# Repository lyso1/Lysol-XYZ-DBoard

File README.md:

# Lysol-XYZ-DBoard
An edited version of the daughter board that was used on XYZ's B-KEN_KO.
This version of the xyz dboard uses the same pinout as c3 unified dboard used on many other boards and other vendors sell. 

This version exists because the original lacked a resetable fuse for over current as well as a diode for some over volt protection. 

There's a pre made panel gerber/project file as well as a BOM and CPL file for JLCPCB prodution and assembly that'll make around 225 dboards from one order at the minimum of 5 panels/pcbs. if you need to change anything bom wise, i'd suggest doing so through the JLCPCB KIcad v6 plugin for easy modifications.

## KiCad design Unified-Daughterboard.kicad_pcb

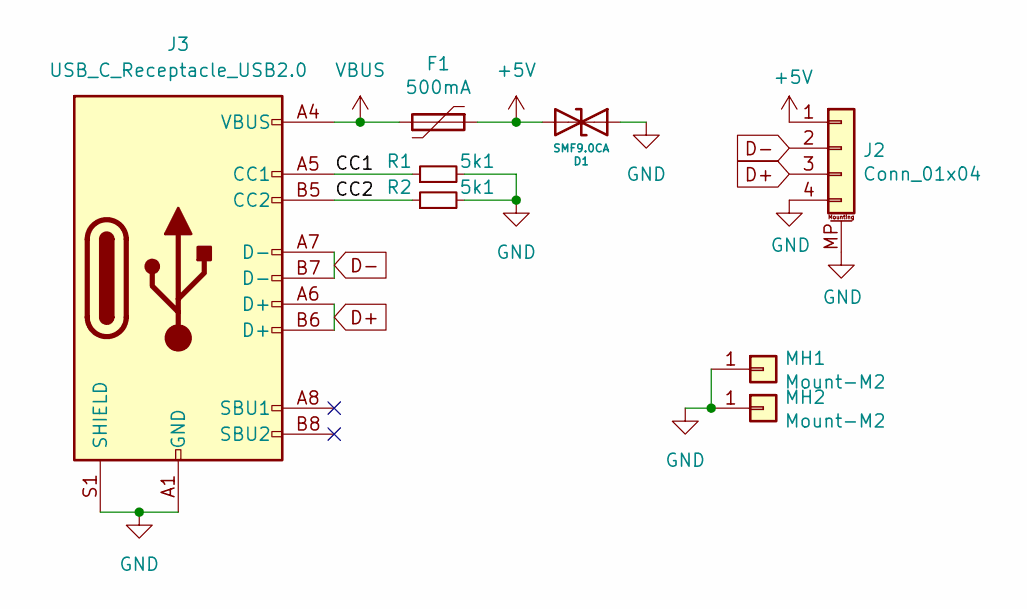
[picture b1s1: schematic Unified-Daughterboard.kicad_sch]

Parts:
D1: SMF9.0CA; D_SOD-123; Manufacturer Part No SMF9.0CA; LCSC Part No C123799
F1: 500mA; Fuse_1206_3216Metric
J2: Conn_01x04; JST-SR-4
J3: USB_C_Receptacle_USB2.0; USB_C_Receptacle_HRO_TYPE-C-31-M-12
MH1, MH2: Mount-M2; MountingHole_3.2mm_M3_Pad_Via
R1, R2: 5k1; R_0402_1005Metric

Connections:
+5V: D1.2 (A2), F1.1, J2.1
/CC1: J3.A5 (CC1), R1.1
/CC2: J3.B5 (CC2), R2.1
D+: J2.3, J3.A6 (D+), J3.B6 (D+)
D-: J2.2, J3.A7 (D-), J3.B7 (D-)
GND: D1.1 (A1), J2.4, J2.MP (MountPin), J3.A1 (GND), J3.A12 (GND), J3.B1 (GND), J3.B12 (GND), J3.S1 (SHIELD), MH1.1, MH2.1, R1.2, R2.2
VBUS: F1.2, J3.A4 (VBUS), J3.A9 (VBUS), J3.B4 (VBUS), J3.B9 (VBUS)

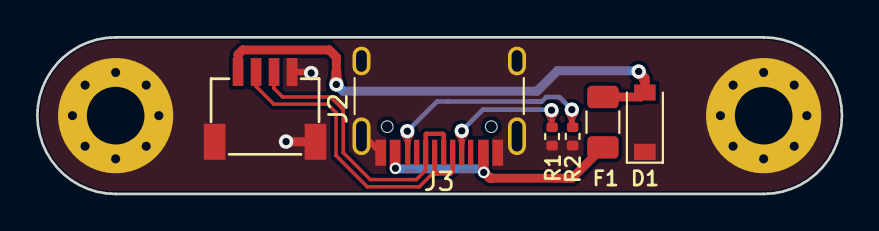
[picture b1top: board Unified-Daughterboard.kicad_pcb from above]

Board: 2 copper layers, 44.7 x 8.7 mm, 8 parts (0 on the bottom side), 7 nets.

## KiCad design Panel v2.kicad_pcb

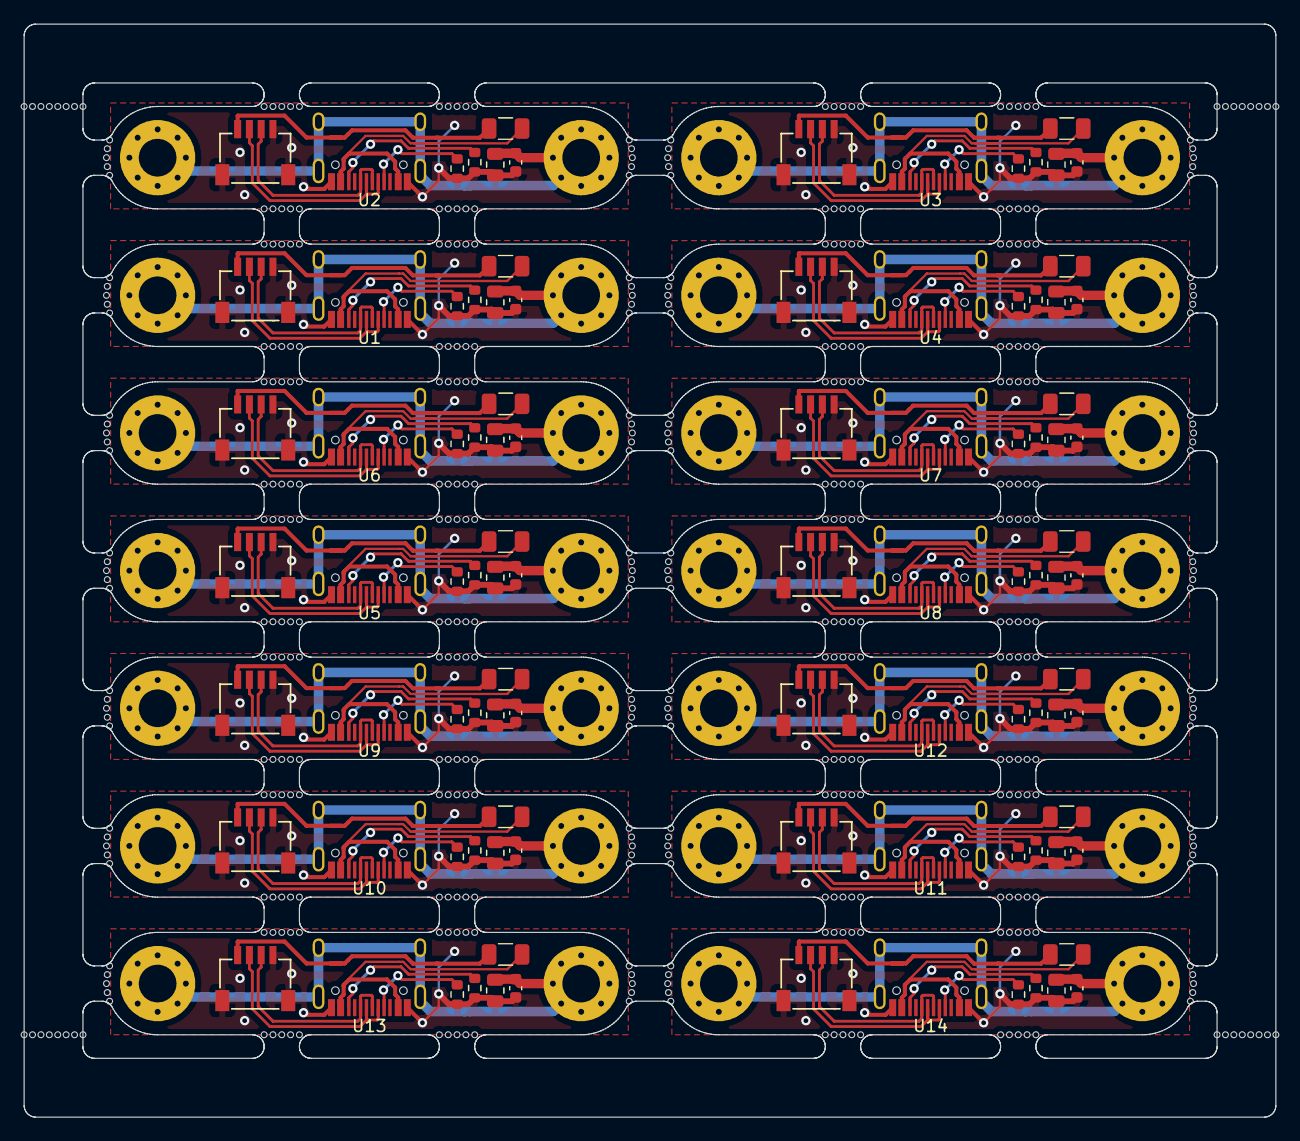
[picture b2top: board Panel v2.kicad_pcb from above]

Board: 2 copper layers, 106.4 x 92.9 mm, 126 parts (0 on the bottom side), 42 nets.

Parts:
C1, C2, C3, C4, C5, C6, C7, C8, C9, C10, C11, C12, C13, C14: 4.7n; C_0603_1608Metric
F1, F2, F3, F4, F5, F6, F7, F8, F9, F10, F11, F12, F13, F14: 500mA; Fuse_1206_3216Metric
J1, J2, J3, J4, J5, J6, J7, J8, J9, J10, J11, J12, J13, J14: Conn_01x04; JST-SR-4
MH1, MH2, MH3, MH4, MH5, MH6, MH7, MH8, MH9, MH10, MH11, MH12, MH13, MH14, MH15, MH16, MH17, MH18, MH19, MH20, MH21, MH22, MH23, MH24, MH25, MH26, MH27, MH28: Mount-M2; MountingHole_3.2mm_M3_Pad_Via
R1, R4, R9, R12, R13, R15, R20, R23, R25, R26, R35, R36, R39, R42: 1M; R_0805_2012Metric
R2, R3, R5, R6, R7, R8, R10, R11, R14, R16, R17, R18, R19, R21, R22, R24, R27, R28, R29, R30, R31, R32, R33, R34, R37, R38, R40, R41: 5.1k; R_0603_1608Metric
U1, U2, U3, U4, U5, U6, U7, U8, U9, U10, U11, U12, U13, U14: HRO-TYPE-C-31-M-12

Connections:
Board_0-+5V: F2.1, J1.1
Board_0-GND: C1.1, J1.4, J1.MP (MountPin), R1.1, R5.2, R6.2
Board_0-SHIELD: C1.2, MH1.1, MH5.1, R1.2
Board_1-+5V: F3.1, J2.1
Board_1-GND: C3.1, J2.4, J2.MP (MountPin), R8.2, R9.1, R11.2
Board_1-SHIELD: C3.2, MH4.1, MH8.1, R9.2
Board_2-+5V: F1.1, J4.1
Board_2-GND: C2.1, J4.4, J4.MP (MountPin), R2.2, R3.2, R4.1
Board_2-SHIELD: C2.2, MH2.1, MH3.1, R4.2
Board_3-+5V: F4.1, J8.1
Board_3-GND: C4.1, J8.4, J8.MP (MountPin), R7.2, R10.2, R12.1
Board_3-SHIELD: C4.2, MH6.1, MH7.1, R12.2
Board_4-+5V: F5.1, J5.1
Board_4-GND: C6.1, J5.4, J5.MP (MountPin), R15.1, R16.2, R17.2
Board_4-SHIELD: C6.2, MH9.1, MH12.1, R15.2
Board_5-+5V: F7.1, J7.1
Board_5-GND: C8.1, J7.4, J7.MP (MountPin), R19.2, R21.2, R23.1
Board_5-SHIELD: C8.2, MH14.1, MH16.1, R23.2
Board_6-+5V: F6.1, J3.1
Board_6-GND: C5.1, J3.4, J3.MP (MountPin), R13.1, R14.2, R18.2
Board_6-SHIELD: C5.2, MH10.1, MH13.1, R13.2
Board_7-+5V: F8.1, J6.1
Board_7-GND: C7.1, J6.4, J6.MP (MountPin), R20.1, R22.2, R24.2
Board_7-SHIELD: C7.2, MH11.1, MH15.1, R20.2
Board_8-+5V: F9.1, J10.1
Board_8-GND: C9.1, J10.4, J10.MP (MountPin), R26.1, R27.2, R30.2
Board_8-SHIELD: C9.2, MH17.1, MH21.1, R26.2
Board_9-+5V: F11.1, J12.1
Board_9-GND: C11.1, J12.4, J12.MP (MountPin), R33.2, R34.2, R36.1
Board_9-SHIELD: C11.2, MH22.1, MH24.1, R36.2
Board_10-+5V: F10.1, J9.1
Board_10-GND: C10.1, J9.4, J9.MP (MountPin), R25.1, R28.2, R29.2
Board_10-SHIELD: C10.2, MH18.1, MH19.1, R25.2
Board_11-+5V: F12.1, J11.1
Board_11-GND: C12.1, J11.4, J11.MP (MountPin), R31.2, R32.2, R35.1
Board_11-SHIELD: C12.2, MH20.1, MH23.1, R35.2
Board_12-+5V: F13.1, J13.1
Board_12-GND: C13.1, J13.4, J13.MP (MountPin), R37.2, R38.2, R39.1
Board_12-SHIELD: C13.2, MH25.1, MH27.1, R39.2
Board_13-+5V: F14.1, J14.1
Board_13-GND: C14.1, J14.4, J14.MP (MountPin), R40.2, R41.2, R42.1
Board_13-SHIELD: C14.2, MH26.1, MH28.1, R42.2

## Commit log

2022-08-14 update dboard
